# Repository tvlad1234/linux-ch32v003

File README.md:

# linux-ch32v003
Linux on a $0.15 RISC-V microcontroller

This project enables the CH32V003 microcontroller to run Linux. It achieves this by using an 8 megabyte SPI PSRAM chip and a RISC-V emulator (the very nice [mini-rv32ima by cnlohr](https://github.com/cnlohr/mini-rv32ima)). The emulation is needed because the PSRAM cannot be mapped into the address space of the microcontroler. The Linux kernel and rootfs is loaded into PSRAM at boot from an SD card. FAT filesystem access is provided by the [Petit FatFs](http://elm-chan.org/fsw/ff/00index_p.html) library.

## How to use
This project uses the [ch32v003fun](https://github.com/cnlohr/ch32v003fun) SDK, which must reside in the same folder where this repository was cloned.

The PSRAM and SD card are connected to the hardware SPI interface of the CH32V003. The chip select pins can be set in the [thing_config.h](thing_config.h) file. The console can be accessed over the UART pins. The SD card containing the [Linux image file](Image) must be formatted as FAT32 or FAT16, and the file must be placed in the root. 

A suggested schematic and corresponding single-layer PCB design can be found in the [hardware](hardware) folder (it's a KiCad 7 project).

Boot time is around 5 minutes. The Linux image includes the coremark benchmark in the `/root/` folder.

## Building the Linux image
If you wish to build your own Linux image, you can do so by running `make linux`. The resulting image will be located in `linux/buildroot/output/images/`.

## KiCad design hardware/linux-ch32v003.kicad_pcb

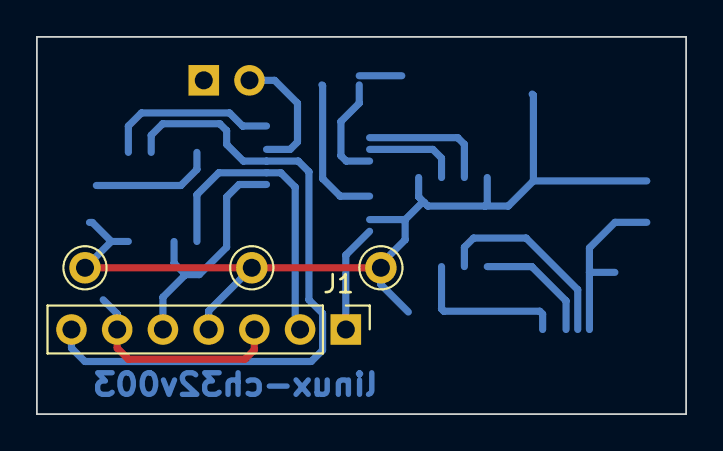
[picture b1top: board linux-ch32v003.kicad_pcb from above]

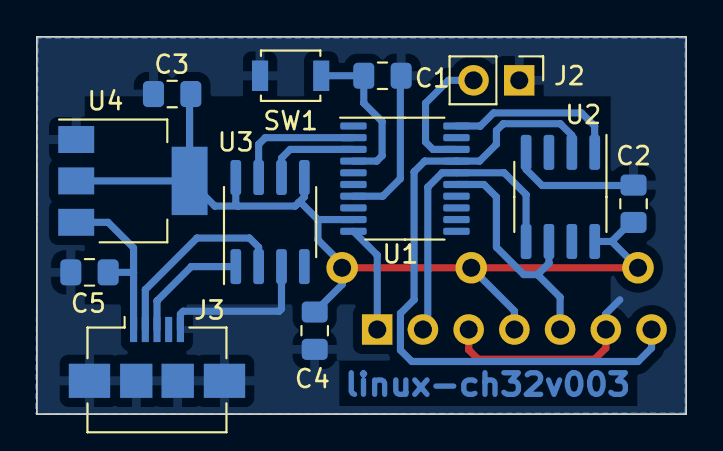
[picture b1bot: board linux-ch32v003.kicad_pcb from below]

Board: 2 copper layers, 36.1 x 21.0 mm, 16 parts (12 on the bottom side), 14 nets.

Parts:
C1, C2, C3, C4, C5: C; C_0805_2012Metric_Pad1.18x1.45mm_HandSolder
J1: SD; PinHeader_1x07_P2.54mm_Vertical
J2: SWIO; PinHeader_1x02_P2.54mm_Vertical
J3: USB_B_Micro; USB_Micro-B_Amphenol_10104110_Horizontal
SW1: SW_Push; SW_SPST_B3U-1000P
TP1, TP2, TP3: TestPoint; TestPoint_THTPad_D2.0mm_Drill1.0mm
U1: CH32V003f4p6; TSSOP-20_4.4x6.5mm_P0.65mm
U2: ESP-PSRAM32; SOIC-8_3.9x4.9mm_P1.27mm
U3: CH330N; SOIC-8_3.9x4.9mm_P1.27mm
U4: AMS1117-3.3; SOT-223-3_TabPin2

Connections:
+3.3V: C2.1, C3.1, C4.1, J1.4, TP1.1, TP2.1, TP3.1, U1.9 (VDD), U2.8 (VCC), U3.5 (VCC), U3.8 (V3), U4.2 (VO)
GND: C1.2, C2.2, C3.2, C4.2, C5.2, J1.3, J1.6, J2.1, J3.5 (GND), J3.6 (Shield), SW1.2, U1.7 (vss), U2.4 (VSS), U3.3 (GND), U4.1 (GND)
LINUX_RX: U1.3 (PD6_A6_UART_RX), U3.6 (TXD)
LINUX_TX: U1.2 (PD5_A5_UART_TX), U3.7 (RXD)
MISO: J1.7, U1.17 (PC7_MISO), U2.2 (SO/SIO)
MOSI: J1.2, U1.16 (PC6_MOSI), U2.5 (SI/SIO)
unnamed: J3.3 (D+), U3.1 (UD+)
unnamed: J3.2 (D-), U3.2 (UD-)
unnamed: C1.1, SW1.1, U1.4 (PD7_NRST_T2CH4)
PSRAM_CS: U1.20 (PD2_A4_T1CH2), U2.1 (~CE)
SCK: J1.5, U1.15 (PC5_SCK), U2.6 (SCLK)
SD_CS: J1.1, U1.10 (PC0_T2CH3)
SWIO: J2.2, U1.18 (SWIO&PD1_T1CH3N)
VBUS: C5.1, J3.1 (VBUS), U4.3 (VI)

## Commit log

2024-02-20 add buildroot config and makefile
2024-02-21 move SD card to HW SPI
2024-02-21 add KiCad project with schematic and PCB
2024-02-23 move PSRAM and SD GPIO initializiation into main
2024-02-23 implement uart character queue
2024-02-24 nicer boot screen, use interrupt for uart receive
2024-02-25 fix incorrect pin label in the schematic symbol
